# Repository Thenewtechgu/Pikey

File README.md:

# Pikey

My verson of a usb rubber ducky that can also be used as a storage device
## The Schematic and board

This is the schematic of the board.

Pikey uses
- RP2350B as the controller and communicater between the chip and the computer
- Flash memory (8mb)
- Micro sd card ( can be used for storage of payload or to be used as a normal flash drive)
- A user configurable Tactile Switch
- A 3 color LED (Red, Blue, Green)

And this is the routed board.

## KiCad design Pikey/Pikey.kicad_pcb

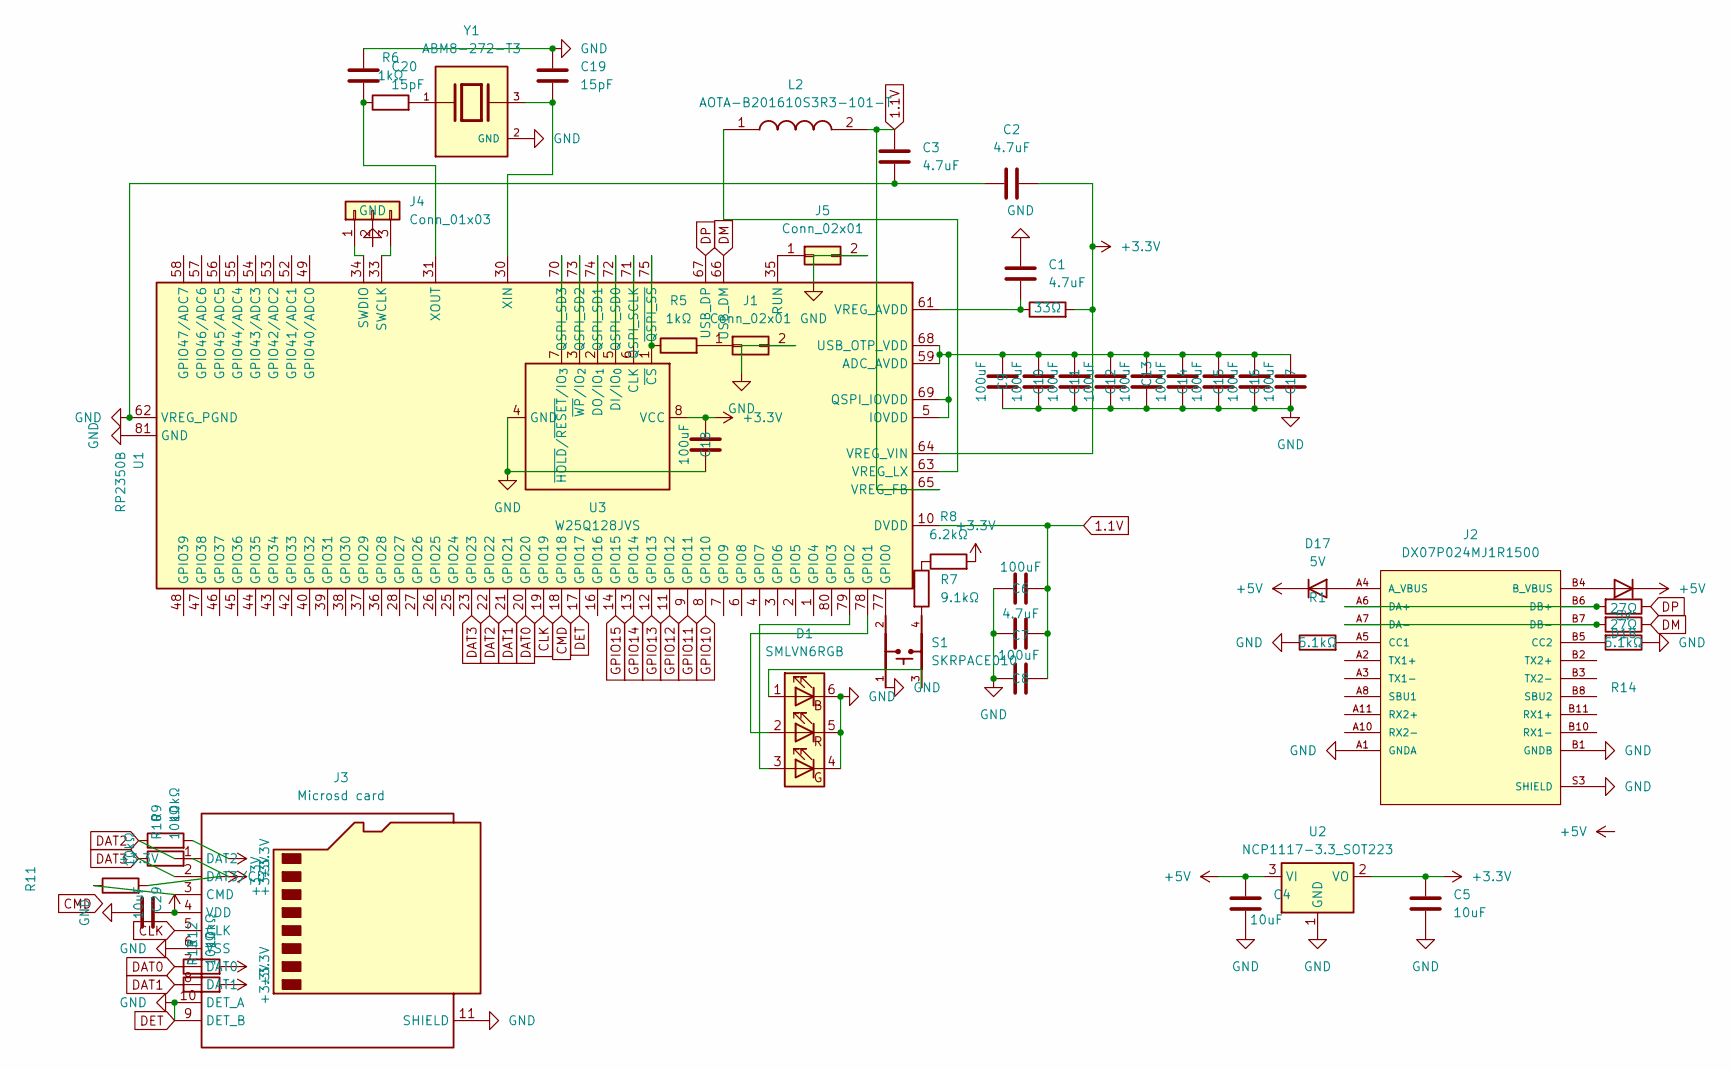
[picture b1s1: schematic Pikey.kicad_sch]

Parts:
C1, C2, C3, C7: 4.7uF; C_0402_1005Metric; LCSC Part number C23733
C4, C5, C29: 10uF; C_0402_1005Metric; LCSC Part number C315248
C6, C8, C9, C10, C11, C12, C13, C14, C15, C16, C17, C18: 100uF; C_0402_1005Metric; LCSC Part number C26409
C19, C20: 15pF; C_0402_1005Metric; LCSC Part number C86285
D1: SMLVN6RGB; LED_ROHM_SMLVN6; LCSC Part number C2909770
D17, D18: 5V; D_0402_1005Metric; LCSC Part number C145179
J1, J5: Conn_02x01; PinHeader_2x01_P1.00mm_Vertical
J2: DX07P024MJ1R1500; JAE_DX07P024MJ1R1500; PARTREV 1.0; LCSC Part number C134112
J3: Microsd card; microSD_HC_Hirose_DM3AT-SF-PEJM5; LCSC Part number C114218
J4: Conn_01x03; PinHeader_1x03_P1.00mm_Vertical
L2: AOTA-B201610S3R3-101-T; AOTAB201610S3R3101T; Manufacturer_Part_Number AOTA-B201610S3R3-101-T; Mouser Part Number 815-AB201610S3R3101T
R1, R14: 5.1kΩ; R_0201_0603Metric; LCSC Part number C105872
R2, R3: 27Ω; R_0201_0603Metric; LCSC Part number C413051
R4: 33Ω; R_0402_1005Metric; LCSC Part number C2906868
R5, R6: 1kΩ; R_0402_1005Metric; LCSC Part number C106235
R7: 9.1kΩ; R_0201_0603Metric; LCSC Part number C163450
R8: 6.2kΩ; R_0201_0603Metric; LCSC Part number C137946
R9, R10, R11, R12, R13: 10kΩ; R_0201_0603Metric; LCSC Part number C60490
S1: SKRPACE010; SW_SKRPACE010; LCSC Part number C139797
U1: RP2350B; QFN-80-1EP_10x10mm_P0.4mm_EP3.4x3.4mm; LCSC Part number C42415655
U2: NCP1117-3.3_SOT223; SOT-223-3_TabPin2; LCSC Part number C26537
U3: W25Q128JVS; SOIC-8_5.3x5.3mm_P1.27mm; LCSC Part number C97521
Y1: ABM8-272-T3; XTAL_ABM8-272-T3; PARTREV 07-29-20; LCSC Part number C20625731

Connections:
1.1V: C3.1, C6.1, C7.1, C8.1, L2.2, U1.10 (DVDD), U1.32 (DVDD), U1.51 (DVDD), U1.65 (VREG_FB)
+3.3V: C2.1, C5.2, C18.1, C29.1, J3.4 (VDD), R4.2, R8.2, R9.2, R10.2, R11.2, R12.2, R13.2, U1.64 (VREG_VIN), U2.2 (VO), U3.8 (VCC)
+5V: C4.2, D17.1 (K), D18.1 (K), U2.3 (VI)
A_VBUS: D17.2 (A), J2.A4 (A_VBUS), J2.A9 (A_VBUS)
B_VBUS: D18.2 (A), J2.B4 (B_VBUS), J2.B9 (B_VBUS)
CLK: J3.5 (CLK), U1.19 (GPIO19)
DAT0: J3.7 (DAT0), R12.1, U1.20 (GPIO20)
DAT1: J3.8 (DAT1), R13.1, U1.21 (GPIO21)
DAT2: J3.1 (DAT2), R9.1, U1.22 (GPIO22)
DAT3: J3.2 (DAT3/CD), R10.1, U1.23 (GPIO23)
DET: C1.1, C2.2, C3.2, C4.1, C5.1, C6.2, C7.2, C8.2, C9.2, C10.2, C11.2, C12.2, C13.2, C14.2, C15.2, C16.2, C17.2, C18.2, C19.1, C20.1, C29.2, D1.4 (GK), D1.5 (RK), D1.6 (BK), J1.2, J2.A1 (GNDA), J2.A12 (GNDA), J2.B1 (GNDB), J2.B12 (GNDB), J2.S3 (SHIELD), J2.S4 (SHIELD), J2.S5 (SHIELD), J2.S6 (SHIELD), J3.6 (VSS), J3.9 (DET_B), J3.10 (DET_A), J3.11 (SHIELD), J4.2, J5.2, R1.1, R14.1, S1.1, U1.17 (GPIO17), U1.62 (VREG_PGND), U1.81 (GND), U2.1 (GND), U3.4 (GND), Y1.2 (GND), Y1.4 (GND)
DM: R2.1, U1.66 (USB_DM)
DP: R3.1, U1.67 (USB_DP)
GPIO10: U1.8 (GPIO10)
GPIO11: U1.9 (GPIO11)
GPIO12: U1.11 (GPIO12)
GPIO13: U1.12 (GPIO13)
GPIO14: U1.13 (GPIO14)
GPIO15: U1.14 (GPIO15)
unnamed: D1.1 (BA), S1.3
unnamed: D1.3 (GA), U1.79 (GPIO2)
unnamed: D1.2 (RA), U1.78 (GPIO1)
unnamed: J1.1, R5.2
unnamed: J2.A5 (CC1), R1.2
unnamed: J2.B5 (CC2), R14.2
unnamed: J2.A6 (DA+), J2.B6 (DB+), R3.2
unnamed: J2.A7 (DA-), J2.B7 (DB-), R2.2
unnamed: J4.1, U1.34 (SWDIO)
unnamed: J4.3, U1.33 (SWCLK)
unnamed: J5.1, U1.35 (RUN)
unnamed: R6.2, Y1.1
unnamed: R7.1, R8.1
unnamed: R7.2, S1.4
unnamed: C9.1, C10.1, C11.1, C12.1, C13.1, C14.1, C15.1, C16.1, C17.1, U1.5 (IOVDD), U1.15 (IOVDD), U1.24 (IOVDD), U1.29 (IOVDD), U1.41 (IOVDD), U1.50 (IOVDD), U1.59 (ADC_AVDD), U1.60 (IOVDD), U1.68 (USB_OTP_VDD), U1.69 (QSPI_IOVDD), U1.76 (IOVDD)
unnamed: S1.2, U1.77 (GPIO0)
unnamed: U1.71 (QSPI_SCLK), U3.6 (CLK)
unnamed: U1.72 (QSPI_SD0), U3.5 (DI/IO_{0})
unnamed: U1.74 (QSPI_SD1), U3.2 (DO/IO_{1})
unnamed: U1.73 (QSPI_SD2), U3.3 (~WP/IO_{2})
unnamed: U1.70 (QSPI_SD3), U3.7 (~HOLD/~RESET/IO_{3})
unnamed: C1.2, R4.1, U1.61 (VREG_AVDD)
unnamed: L2.1, U1.63 (VREG_LX)
unnamed: C19.2, U1.30 (XIN), Y1.3
unnamed: C20.2, R6.1, U1.31 (XOUT)
unnamed: R5.1, U1.75 (~QSPI_SS), U3.1 (~CS)

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
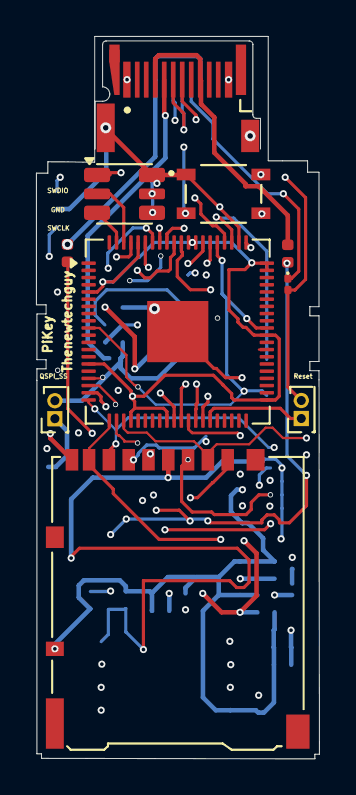
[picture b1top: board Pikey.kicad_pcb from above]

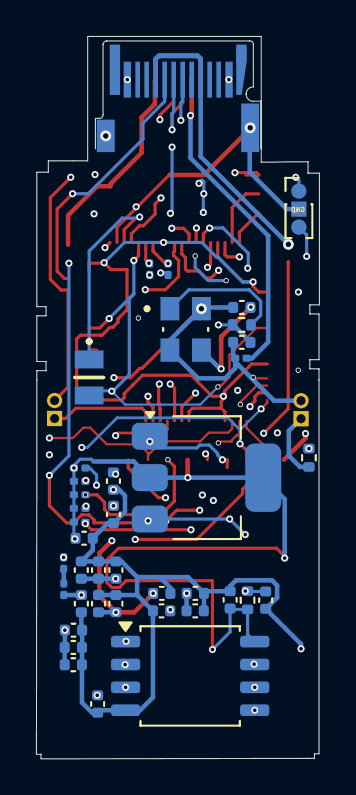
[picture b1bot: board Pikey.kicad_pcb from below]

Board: 4 copper layers, 15.7 x 40.1 mm, 49 parts (39 on the bottom side), 40 nets.

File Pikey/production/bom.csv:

Designator,Footprint,Quantity,Value,LCSC Part #
"C1, C2, C3, C7",0402,4,4.7uF,
"C10, C11, C12, C13, C14, C15, C16, C17, C18, C6, C8, C9",0402,12,100uF,
"C19, C20",0402,2,15pF,
"C29, C4, C5",0402,3,10uF,
D1,LED_ROHM_SMLVN6,1,SMLVN6RGB,
"D17, D18",0402,2,5V,
J1,JAE_DX07P024AJ1R1500,1,DX07P024AJ1R1500,
J3,microSD_HC_Hirose_DM3AT-SF-PEJM5,1,Microsd card,
R1,0201,1,5.1kΩ,
"R10, R11, R12, R13, R9",0201,5,10kΩ,
"R2, R3",0201,2,27Ω,
R4,0402,1,33Ω,
"R5, R6",0402,2,1kΩ,
R7,0201,1,9.1kΩ,
R8,0201,1,6.2kΩ,
S1,SW_SKRPACE010,1,SKRPACE010,
"SW1, SW2",SW_SPST_CK_KMS2xxGP,2,CK_KMS2xxG,
U1,QFN-80-1EP_10x10mm_P0.4mm_EP3.4x3.4mm,1,RP2350B,
U2,SOT-223-3_TabPin2,1,NCP1117-3.3_SOT223,
U3,SOIC-8_5.3x5.3mm_P1.27mm,1,W25Q128JVS,
Y1,XTAL_ABM8-272-T3,1,ABM8-272-T3,

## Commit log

2026-04-07 setup
2026-04-07 removed the wrong files
2026-04-10 Add journal entry for usb-c connector search
    Documented the search for a usb-c male connector with Kicad library.
2026-04-10 Rename Journal.md to JOURNAL.md
2026-04-10 Update date entry format in JOURNAL.md
    Changed the heading format for the date entry.
2026-04-11 Update JOURNAL.md with RP2350B parts and time
    Added details about required parts for RP2350B and updated time spent.
2026-04-11 Update JOURNAL.md with RP2350B component details
    Added detailed notes and images for components related to the RP2350B project, including voltage regulator, USB-C power supply, capacitors, flash memory, crystal oscillator, debug connector, and rese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
2026-04-11 11th April 2026 update
2026-04-12 Revise JOURNAL.md with new entries and images
    Updated journal entries with images and additional details for various components including voltage regulator, USB-C power supply, and sd card holder.
2026-04-12 Sunday 12th April update
2026-04-13 Add entry for Bluetooth module installation
    Documented the addition of a Bluetooth module and the time spent on the task.
2026-04-13 13th April update
    added the nRF8001
2026-04-13 Gitinorge
2026-04-14 Update JOURNAL.md with BOM file creation details
    Documented the process of creating the BOM file and noted issues encountered.
2026-04-14 Update journal with note on Bluetooth chip decision
    Added a note about reconsidering the Bluetooth chip for financial reasons.
2026-04-14 Update JOURNAL.md with April 14th entries
    Added time spent entry and notes for April 14th.
2026-04-18 updateee
2026-04-18 Convert time spent format to decimal hours
    Updated time spent entries to use decimal hours instead of minutes.
2026-04-20 Update JOURNAL.md with new considiration
    Document decision to remove the Bluetooth chip for space considerations.
2026-04-20 20th april update
2026-04-27 Add journal entry for Monday 27th April
    Added new journal entry for Monday 27th April with images and time spent.
2026-04-27 Update time spent on project
    Updated time spent on project from 0.5 to 0.75 hours.
2026-04-29 Document progress for April 29th
    Added progress update and images for April 29th.
2026-05-01 Update JOURNAL.md with new entries and images
    Added new entries for Thursday 30th April and Friday 1st May, including images and time spent.
2026-05-02 Add journal entry for Saturday 2nd May
    Added journal entry for Saturday 2nd May with images and time spent.
2026-05-02 Update JOURNAL.md with new content and images
    Added text and a QR code to the GitHub page, along with updated time spent.
2026-05-02 May 2nd update
2026-05-04 Enhance README with project details and schematics
    Expanded project description and added schematic details.
2026-05-04 Update JOURNAL with recent changes
    Document updates made to the Readme and production files.
2026-05-04 Monday 4th May update
